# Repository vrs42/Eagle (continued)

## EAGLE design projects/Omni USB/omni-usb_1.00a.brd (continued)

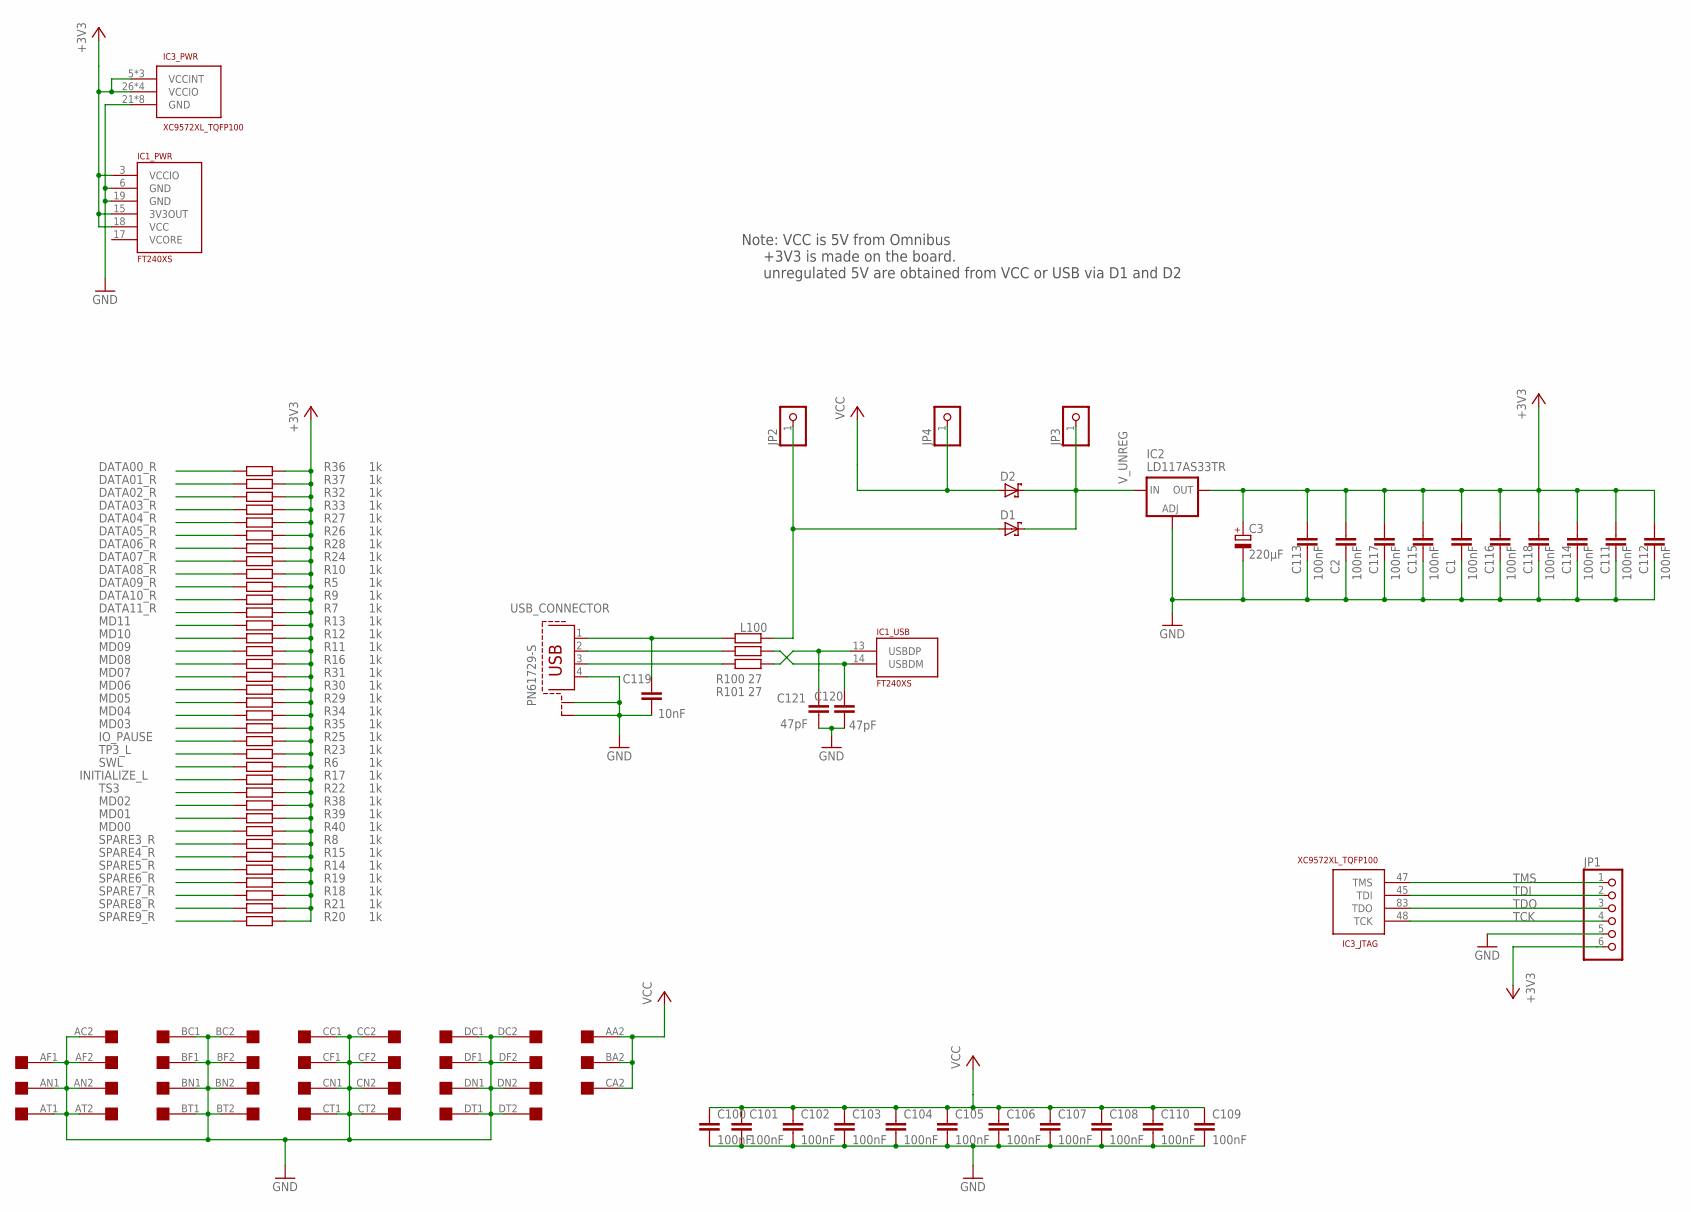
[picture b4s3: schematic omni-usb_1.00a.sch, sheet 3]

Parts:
C1, C2, C100, C101, C102, C103, C104, C105, C106, C107, C108, C109, C110, C111, C112, C113, C114, C115, C116, C117, C118: 100nF; C0805; MPN 08053C104KAT2A
C3: 220µF; SANYO-OSCON_SMD_F8; MPN MCEEL10V227M8X10.5
C119: 10nF; C0805; MPN 08055C103KAT2A
C120, C121: 47pF; C0805; MPN MCCA000326
D1, D2: SCHOTTKY-DIODESMD; SMB; MPN BAT165
IC1: FT240XS; TSSOP24; MPN FT240XS
IC2: LD117AS33TR; SOT223; MPN TLV1117-33CDCY
IC3: XC9572XL_TQFP100; TQ100; MPN XC9572XL-10TQG100C
JP1: PINHD-1X6/90; 1X06/90; MPN MC34751
JP2, JP3, JP4: PINHD-1X1; 1X01
L100: R-EU_R0805; R0805
R5, R6, R7, R8, R9, R10, R11, R12, R13, R14, R15, R16, R17, R18, R19, R20, R21, R22, R23, R24, R25, R26, R27, R28, R29, R30, R31, R32, R33, R34, R35, R36, R37, R38, R39, R40: 1k; R0805; MPN ERJ6GEYJ102V
R100, R101: 27; R0805; MPN ERJ6ENF2742V
U$2: QUAD; EDGE-CON8
USB_CONNECTOR: PN61729-S; MPN MC32596

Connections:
+3V3: C1.1, C2.1, C3.+, C111.1, C112.1, C113.1, C114.1, C115.1, C116.1, C117.1, C118.1, IC1.3 (VCCIO), IC1.15 (3V3OUT), IC1.18 (VCC), IC2.4 (OUT), IC3.5 (VCCINT), IC3.26 (VCCIO), IC3.38 (VCCIO), IC3.51 (VCCIO), IC3.57 (VCCINT), IC3.88 (VCCIO), IC3.98 (VCCINT), JP1.6, R5.1, R6.1, R7.1, R8.1, R9.1, R10.1, R11.1, R12.1, R13.1, R14.1, R15.1, R16.1, R17.1, R18.1, R19.1, R20.1, R21.1, R22.1, R23.1, R24.1, R25.1, R26.1, R27.1, R28.1, R29.1, R30.1, R31.1, R32.1, R33.1, R34.1, R35.1, R36.1, R37.1, R38.1, R39.1, R40.1; also elsewhere on the board
DATA00_R: R36.2; also elsewhere on the board
DATA01_R: R37.2; also elsewhere on the board
DATA02_R: R32.2; also elsewhere on the board
DATA03_R: R33.2; also elsewhere on the board
DATA04_R: R27.2; also elsewhere on the board
DATA05_R: R26.2; also elsewhere on the board
DATA06_R: R28.2; also elsewhere on the board
DATA07_R: R24.2; also elsewhere on the board
DATA08_R: R10.2; also elsewhere on the board
DATA09_R: R5.2; also elsewhere on the board
DATA10_R: R9.2; also elsewhere on the board
DATA11_R: R7.2; also elsewhere on the board
GND: C1.2, C2.2, C3.-, C100.2, C101.2, C102.2, C103.2, C104.2, C105.2, C106.2, C107.2, C108.2, C109.2, C110.2, C111.2, C112.2, C113.2, C114.2, C115.2, C116.2, C117.2, C118.2, C119.2, C120.2, C121.2, IC1.6 (GND), IC1.19 (GND), IC2.1 (ADJ), IC3.21 (GND), IC3.31 (GND), IC3.44 (GND), IC3.62 (GND), IC3.69 (GND), IC3.75 (GND), IC3.84 (GND), IC3.100 (GND), JP1.5, U$2.AC2, U$2.AF1, U$2.AF2, U$2.AN1, U$2.AN2, U$2.AT1, U$2.AT2, U$2.BC1, U$2.BC2, U$2.BF1, U$2.BF2, U$2.BN1, U$2.BN2, U$2.BT1, U$2.BT2, U$2.CC1, U$2.CC2, U$2.CF1, U$2.CF2, U$2.CN1, U$2.CN2, U$2.CT1, U$2.CT2, U$2.DC1, U$2.DC2, U$2.DF1, U$2.DF2, U$2.DN1, U$2.DN2, U$2.DT1, U$2.DT2, USB_CONNECTOR.4, USB_CONNECTOR.S1, USB_CONNECTOR.S2; also elsewhere on the board
INITIALIZE_L: R17.2; also elsewhere on the board
IO_PAUSE: R25.2; also elsewhere on the board
MD00: R40.2; also elsewhere on the board
MD01: R39.2; also elsewhere on the board
MD02: R38.2; also elsewhere on the board
MD03: R35.2; also elsewhere on the board
MD04: R34.2; also elsewhere on the board
MD05: R29.2; also elsewhere on the board
MD06: R30.2; also elsewhere on the board
MD07: R31.2; also elsewhere on the board
MD08: R16.2; also elsewhere on the board
MD09: R11.2; also elsewhere on the board
MD10: R12.2; also elsewhere on the board
MD11: R13.2; also elsewhere on the board
unnamed: C121.1, IC1.13 (USBDP), R101.2
unnamed: C119.1, L100.2, USB_CONNECTOR.1
unnamed: C120.1, IC1.14 (USBDM), R100.2
unnamed: R100.1, USB_CONNECTOR.2
unnamed: R101.1, USB_CONNECTOR.3
SPARE3_R: R8.2; also elsewhere on the board
SPARE4_R: R15.2; also elsewhere on the board
SPARE5_R: R14.2; also elsewhere on the board
SPARE6_R: R19.2; also elsewhere on the board
SPARE7_R: R18.2; also elsewhere on the board
SPARE8_R: R21.2; also elsewhere on the board
SPARE9_R: R20.2; also elsewhere on the board
SWL: R6.2; also elsewhere on the board
TCK: IC3.48 (TCK), JP1.4
TDI: IC3.45 (TDI), JP1.2
TDO: IC3.83 (TDO), JP1.3
TMS: IC3.47 (TMS), JP1.1
TP3_L: R23.2; also elsewhere on the board
TS3: R22.2; also elsewhere on the board
VCC: C100.1, C101.1, C102.1, C103.1, C104.1, C105.1, C106.1, C107.1, C108.1, C109.1, C110.1, D2.A, JP4.1, U$2.AA2, U$2.BA2, U$2.CA2; also elsewhere on the board
V_UNREG: D1.C, D2.C, IC2.3 (IN), JP3.1
V_USB: D1.A, JP2.1, L100.1

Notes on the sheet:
Note: VCC is 5V from Omnibus +3V3 is made on the board. unregulated 5V are obtained from VCC or USB via D1 and D2

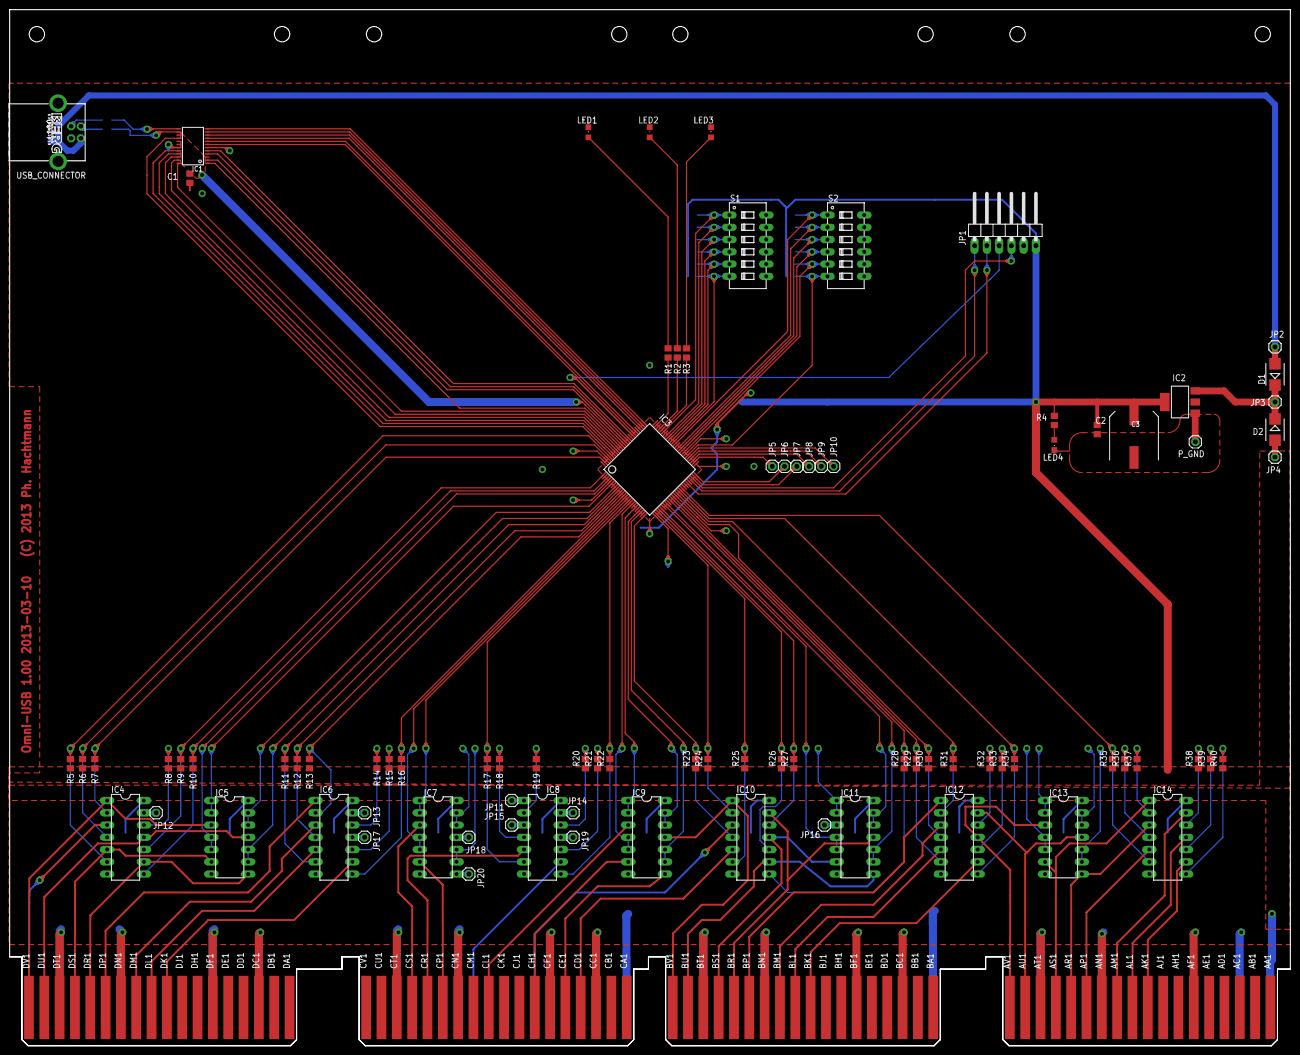
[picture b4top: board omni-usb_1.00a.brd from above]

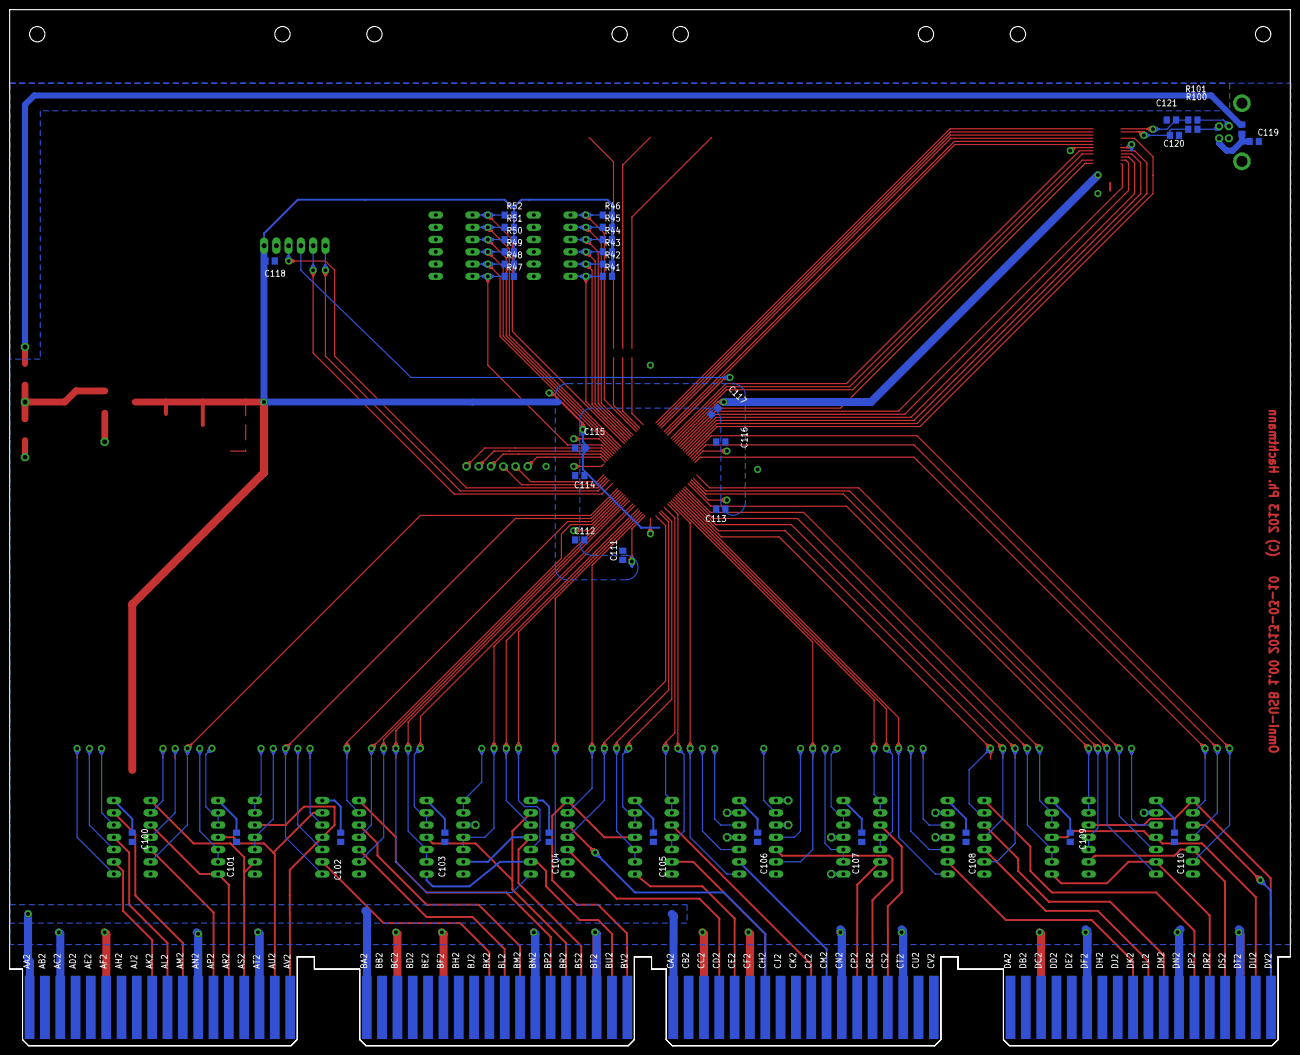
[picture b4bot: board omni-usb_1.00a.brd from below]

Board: 2 copper layers, 265.3 x 214.6 mm, 126 parts (37 on the bottom side), 155 nets.

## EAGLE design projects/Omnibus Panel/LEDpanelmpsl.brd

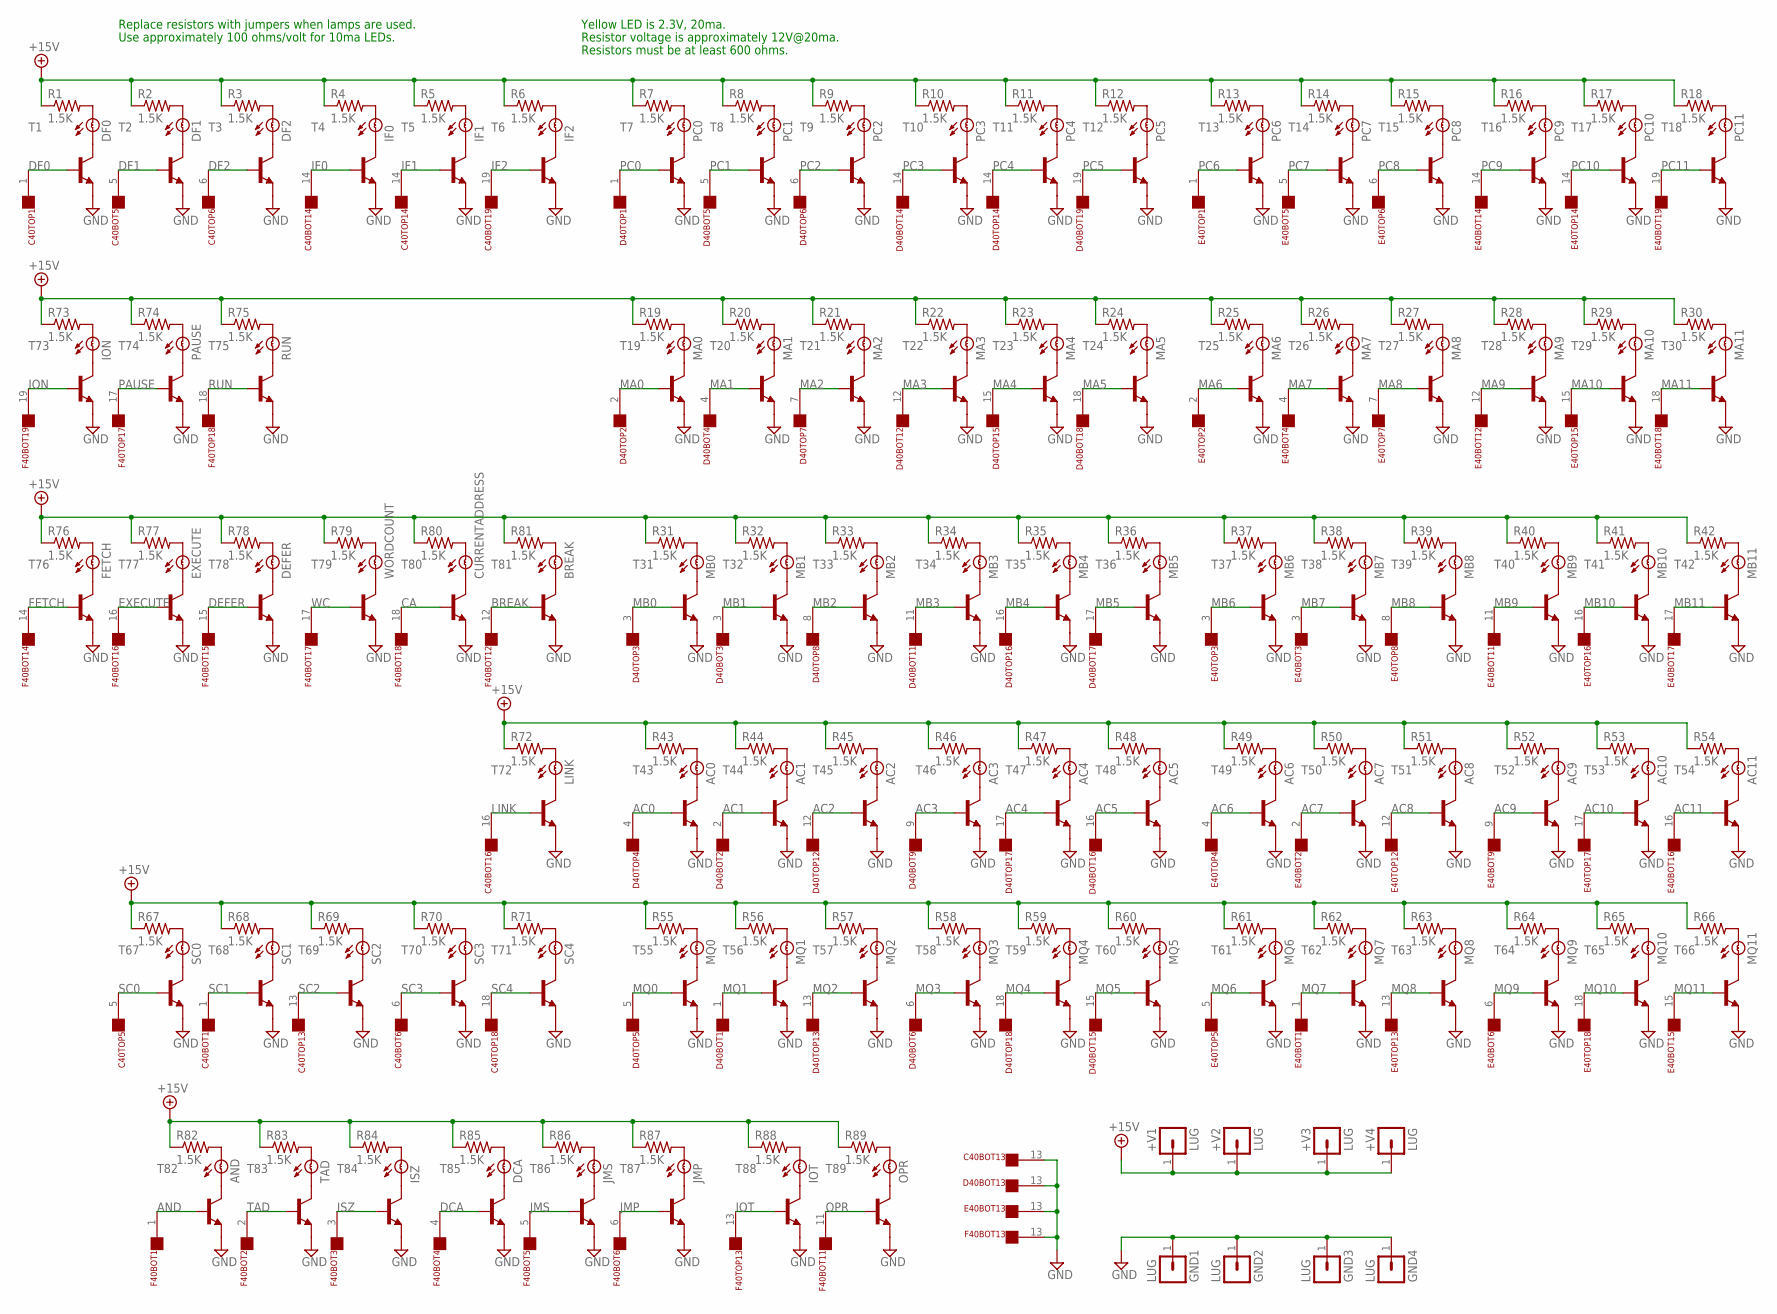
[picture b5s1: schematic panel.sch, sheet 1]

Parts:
+V1, +V2, +V3, +V4: LUG; SPADELUG
AC0, AC1, AC2, AC3, AC4, AC5, AC6, AC7, AC8, AC9, AC10, AC11: BULB
AND: BULB
BREAK: BULB
C40BOT, C40TOP: FLEX19
CURRENTADDRESS: BULB
D40BOT, D40TOP: FLEX19
DCA: BULB
DEFER: BULB
DF0, DF1, DF2: BULB
E40BOT, E40TOP: FLEX19
EXECUTE: BULB
F40BOT, F40TOP: FLEX19
FETCH: BULB
GND1, GND2, GND3, GND4: LUG; SPADELUG
IF0, IF1, IF2: BULB
ION: BULB
IOT: BULB
ISZ: BULB
JMP: BULB
JMS: BULB
LINK: BULB
MA0, MA1, MA2, MA3, MA4, MA5, MA6, MA7, MA8, MA9, MA10, MA11: BULB
MB0, MB1, MB2, MB3, MB4, MB5, MB6, MB7, MB8, MB9, MB10, MB11: BULB
MQ0, MQ1, MQ2, MQ3, MQ4, MQ5, MQ6, MQ7, MQ8, MQ9, MQ10, MQ11: BULB
OPR: BULB
PAUSE: BULB
PC0, PC1, PC2, PC3, PC4, PC5, PC6, PC7, PC8, PC9, PC10, PC11: BULB
R1, R2, R3, R4, R5, R6, R7, R8, R9, R10, R11, R12, R13, R14, R15, R16, R17, R18, R19, R20, R21, R22, R23, R24, R25, R26, R27, R28, R29, R30, R31, R32, R33, R34, R35, R36, R37, R38, R39, R40, R41, R42, R43, R44, R45, R46, R47, R48, R49, R50, R51, R52, R53, R54, R55, R56, R57, R58, R59, R60, R61, R62, R63, R64, R65, R66, R67, R68, R69, R70, R71, R72, R73, R74, R75, R76, R77, R78, R79, R80, R81, R82, R83, R84, R85, R86, R87, R88, R89: 1.5K; 0207/10
RUN: BULB
SC0, SC1, SC2, SC3, SC4: BULB
T1, T2, T3, T4, T5, T6, T7, T8, T9, T10, T11, T12, T13, T14, T15, T16, T17, T18, T19, T20, T21, T22, T23, T24, T25, T26, T27, T28, T29, T30, T31, T32, T33, T34, T35, T36, T37, T38, T39, T40, T41, T42, T43, T44, T45, T46, T47, T48, T49, T50, T51, T52, T53, T54, T55, T56, T57, T58, T59, T60, T61, T62, T63, T64, T65, T66, T67, T68, T69, T70, T71, T72, T73, T74, T75, T76, T77, T78, T79, T80, T81, T82, T83, T84, T85, T86, T87, T88, T89: MPS2222A-NPN-TO92-CBE; TO92-CBE
TAD: BULB
WORDCOUNT: BULB

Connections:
+15V: +V1.1, +V2.1, +V3.1, +V4.1, R1.1, R2.1, R3.1, R4.1, R5.1, R6.1, R7.1, R8.1, R9.1, R10.1, R11.1, R12.1, R13.1, R14.1, R15.1, R16.1, R17.1, R18.1, R19.1, R20.1, R21.1, R22.1, R23.1, R24.1, R25.1, R26.1, R27.1, R28.1, R29.1, R30.1, R31.1, R32.1, R33.1, R34.1, R35.1, R36.1, R37.1, R38.1, R39.1, R40.1, R41.1, R42.1, R43.1, R44.1, R45.1, R46.1, R47.1, R48.1, R49.1, R50.1, R51.1, R52.1, R53.1, R54.1, R55.1, R56.1, R57.1, R58.1, R59.1, R60.1, R61.1, R62.1, R63.1, R64.1, R65.1, R66.1, R67.1, R68.1, R69.1, R70.1, R71.1, R72.1, R73.1, R74.1, R75.1, R76.1, R77.1, R78.1, R79.1, R80.1, R81.1, R82.1, R83.1, R84.1, R85.1, R86.1, R87.1, R88.1, R89.1
AC0: D40TOP.4, T43.B; also elsewhere on the board
AC1: D40BOT.2, T44.B; also elsewhere on the board
AC2: D40TOP.12, T45.B; also elsewhere on the board
AC3: D40BOT.9, T46.B; also elsewhere on the board
AC4: D40TOP.17, T47.B; also elsewhere on the board
AC5: D40BOT.16, T48.B; also elsewhere on the board
AC6: E40TOP.4, T49.B; also elsewhere on the board
AC7: E40BOT.2, T50.B; also elsewhere on the board
AC8: E40TOP.12, T51.B; also elsewhere on the board
AC9: E40BOT.9, T52.B; also elsewhere on the board
AC10: E40TOP.17, T53.B; also elsewhere on the board
AC11: E40BOT.16, T54.B; also elsewhere on the board
AND: F40BOT.1, T82.B; also elsewhere on the board
BREAK: F40BOT.12, T81.B; also elsewhere on the board
CA: F40BOT.18, T80.B; also elsewhere on the board
DCA: F40BOT.4, T85.B; also elsewhere on the board
DEFER: F40BOT.15, T78.B; also elsewhere on the board
DF0: C40TOP.1, T1.B; also elsewhere on the board
DF1: C40BOT.5, T2.B; also elsewhere on the board
DF2: C40TOP.6, T3.B; also elsewhere on the board
EXECUTE: F40BOT.16, T77.B; also elsewhere on the board
FETCH: F40BOT.14, T76.B; also elsewhere on the board
GND: C40BOT.13, D40BOT.13, E40BOT.13, F40BOT.13, GND1.1, GND2.1, GND3.1, GND4.1, T1.E, T2.E, T3.E, T4.E, T5.E, T6.E, T7.E, T8.E, T9.E, T10.E, T11.E, T12.E, T13.E, T14.E, T15.E, T16.E, T17.E, T18.E, T19.E, T20.E, T21.E, T22.E, T23.E, T24.E, T25.E, T26.E, T27.E, T28.E, T29.E, T30.E, T31.E, T32.E, T33.E, T34.E, T35.E, T36.E, T37.E, T38.E, T39.E, T40.E, T41.E, T42.E, T43.E, T44.E, T45.E, T46.E, T47.E, T48.E, T49.E, T50.E, T51.E, T52.E, T53.E, T54.E, T55.E, T56.E, T57.E, T58.E, T59.E, T60.E, T61.E, T62.E, T63.E, T64.E, T65.E, T66.E, T67.E, T68.E, T69.E, T70.E, T71.E, T72.E, T73.E, T74.E, T75.E, T76.E, T77.E, T78.E, T79.E, T80.E, T81.E, T82.E, T83.E, T84.E, T85.E, T86.E, T87.E, T88.E, T89.E; also elsewhere on the board
IF0: C40BOT.14, T4.B; also elsewhere on the board
IF1: C40TOP.14, T5.B; also elsewhere on the board
IF2: C40BOT.19, T6.B; also elsewhere on the board
ION: F40BOT.19, T73.B; also elsewhere on the board
IOT: F40TOP.13, T88.B; also elsewhere on the board
ISZ: F40BOT.3, T84.B; also elsewhere on the board
JMP: F40BOT.6, T87.B; also elsewhere on the board
JMS: F40BOT.5, T86.B; also elsewhere on the board
LINK: C40BOT.16, T72.B; also elsewhere on the board
MA0: D40TOP.2, T19.B; also elsewhere on the board
MA1: D40BOT.4, T20.B; also elsewhere on the board
MA2: D40TOP.7, T21.B; also elsewhere on the board
MA3: D40BOT.12, T22.B; also elsewhere on the board
MA4: D40TOP.15, T23.B; also elsewhere on the board
MA5: D40BOT.18, T24.B; also elsewhere on the board
MA6: E40TOP.2, T25.B; also elsewhere on the board
MA7: E40BOT.4, T26.B; also elsewhere on the board
MA8: E40TOP.7, T27.B; also elsewhere on the board
MA9: E40BOT.12, T28.B; also elsewhere on the board
MA10: E40TOP.15, T29.B; also elsewhere on the board
MA11: E40BOT.18, T30.B; also elsewhere on the board
MB0: D40TOP.3, T31.B; also elsewhere on the board
MB1: D40BOT.3, T32.B; also elsewhere on the board
MB2: D40TOP.8, T33.B; also elsewhere on the board
MB3: D40BOT.11, T34.B; also elsewhere on the board
MB4: D40TOP.16, T35.B; also elsewhere on the board
MB5: D40BOT.17, T36.B; also elsewhere on the board
MB6: E40TOP.3, T37.B; also elsewhere on the board
MB7: E40BOT.3, T38.B; also elsewhere on the board
MB8: E40TOP.8, T39.B; also elsewhere on the board
MB9: E40BOT.11, T40.B; also elsewhere on the board
MB10: E40TOP.16, T41.B; also elsewhere on the board
MB11: E40BOT.17, T42.B; also elsewhere on the board
MQ0: D40TOP.5, T55.B; also elsewhere on the board
MQ1: D40BOT.1, T56.B; also elsewhere on the board
MQ2: D40TOP.13, T57.B; also elsewhere on the board
MQ3: D40BOT.6, T58.B; also elsewhere on the board
MQ4: D40TOP.18, T59.B; also elsewhere on the board
MQ5: D40BOT.15, T60.B; also elsewhere on the board
MQ6: E40TOP.5, T61.B; also elsewhere on the board
MQ7: E40BOT.1, T62.B; also elsewhere on the board
MQ8: E40TOP.13, T63.B; also elsewhere on the board
MQ9: E40BOT.6, T64.B; also elsewhere on the board
MQ10: E40TOP.18, T65.B; also elsewhere on the board
MQ11: E40BOT.15, T66.B; also elsewhere on the board
unnamed: DF0.B, T1.C
unnamed: DF1.B, T2.C
unnamed: DF2.B, T3.C
unnamed: IF0.B, T4.C
unnamed: IF1.B, T5.C
unnamed: IF2.B, T6.C
unnamed: PC0.B, T7.C
unnamed: PC1.B, T8.C
unnamed: PC2.B, T9.C
unnamed: PC3.B, T10.C
unnamed: PC4.B, T11.C
unnamed: PC5.B, T12.C
unnamed: PC6.B, T13.C
unnamed: PC7.B, T14.C
unnamed: PC8.B, T15.C
unnamed: PC9.B, T16.C
unnamed: PC10.B, T17.C
unnamed: PC11.B, T18.C
unnamed: MA0.B, T19.C
unnamed: MA1.B, T20.C
unnamed: MA2.B, T21.C
unnamed: MA3.B, T22.C
unnamed: MA4.B, T23.C
unnamed: MA5.B, T24.C
unnamed: MA6.B, T25.C
unnamed: MA7.B, T26.C
unnamed: MA8.B, T27.C
unnamed: MA9.B, T28.C
unnamed: MA10.B, T29.C
unnamed: MA11.B, T30.C
unnamed: MB0.B, T31.C
unnamed: MB1.B, T32.C
unnamed: MB2.B, T33.C
unnamed: MB3.B, T34.C
unnamed: MB4.B, T35.C
unnamed: MB5.B, T36.C
unnamed: MB6.B, T37.C
unnamed: MB7.B, T38.C
unnamed: MB8.B, T39.C
unnamed: MB9.B, T40.C
unnamed: MB10.B, T41.C
unnamed: MB11.B, T42.C
unnamed: AC0.B, T43.C
unnamed: AC1.B, T44.C
unnamed: AC2.B, T45.C
unnamed: AC3.B, T46.C
unnamed: AC4.B, T47.C
unnamed: AC5.B, T48.C
unnamed: AC6.B, T49.C
unnamed: AC7.B, T50.C
unnamed: AC8.B, T51.C
unnamed: AC9.B, T52.C
unnamed: AC10.B, T53.C
unnamed: AC11.B, T54.C
unnamed: MQ0.B, T55.C
unnamed: MQ1.B, T56.C
unnamed: MQ2.B, T57.C
unnamed: MQ3.B, T58.C
unnamed: MQ4.B, T59.C
unnamed: MQ5.B, T60.C
unnamed: MQ6.B, T61.C
unnamed: MQ7.B, T62.C
unnamed: MQ8.B, T63.C
unnamed: MQ9.B, T64.C
unnamed: MQ10.B, T65.C
unnamed: MQ11.B, T66.C
unnamed: SC0.B, T67.C
unnamed: SC1.B, T68.C
unnamed: SC2.B, T69.C
unnamed: SC3.B, T70.C
unnamed: SC4.B, T71.C
unnamed: LINK.B, T72.C
unnamed: ION.B, T73.C
unnamed: PAUSE.B, T74.C
unnamed: RUN.B, T75.C
unnamed: FETCH.B, T76.C
unnamed: EXECUTE.B, T77.C
unnamed: DEFER.B, T78.C
unnamed: T79.C, WORDCOUNT.B
unnamed: CURRENTADDRESS.B, T80.C
unnamed: BREAK.B, T81.C
unnamed: AND.B, T82.C
unnamed: T83.C, TAD.B
unnamed: ISZ.B, T84.C
unnamed: DCA.B, T85.C
unnamed: JMS.B, T86.C
unnamed: JMP.B, T87.C
unnamed: IOT.B, T88.C
unnamed: OPR.B, T89.C
unnamed: DF0.A, R1.2
unnamed: DF1.A, R2.2
unnamed: DF2.A, R3.2
unnamed: IF0.A, R4.2
unnamed: IF1.A, R5.2
unnamed: IF2.A, R6.2
unnamed: PC0.A, R7.2
unnamed: PC1.A, R8.2
unnamed: PC2.A, R9.2
unnamed: PC3.A, R10.2
unnamed: PC4.A, R11.2
unnamed: PC5.A, R12.2
unnamed: PC6.A, R13.2
unnamed: PC7.A, R14.2
unnamed: PC8.A, R15.2
unnamed: PC9.A, R16.2
unnamed: PC10.A, R17.2
unnamed: PC11.A, R18.2
unnamed: ION.A, R73.2
unnamed: PAUSE.A, R74.2
unnamed: R75.2, RUN.A
unnamed: MA0.A, R19.2
unnamed: MA1.A, R20.2
unnamed: MA2.A, R21.2
unnamed: MA3.A, R22.2
unnamed: MA4.A, R23.2
unnamed: MA5.A, R24.2
unnamed: MA6.A, R25.2
unnamed: MA7.A, R26.2
unnamed: MA8.A, R27.2
unnamed: MA9.A, R28.2
unnamed: MA10.A, R29.2
unnamed: MA11.A, R30.2
unnamed: FETCH.A, R76.2
unnamed: EXECUTE.A, R77.2
unnamed: DEFER.A, R78.2
unnamed: R79.2, WORDCOUNT.A
unnamed: CURRENTADDRESS.A, R80.2
unnamed: BREAK.A, R81.2
unnamed: LINK.A, R72.2
unnamed: MB0.A, R31.2
unnamed: MB1.A, R32.2
unnamed: MB2.A, R33.2
unnamed: MB3.A, R34.2
unnamed: MB4.A, R35.2
unnamed: MB5.A, R36.2
unnamed: MB6.A, R37.2
unnamed: MB7.A, R38.2
unnamed: MB8.A, R39.2
unnamed: MB9.A, R40.2
unnamed: MB10.A, R41.2
unnamed: MB11.A, R42.2
unnamed: AC0.A, R43.2
unnamed: AC1.A, R44.2
unnamed: AC2.A, R45.2
unnamed: AC3.A, R46.2
unnamed: AC4.A, R47.2
unnamed: AC5.A, R48.2
unnamed: AC6.A, R49.2
unnamed: AC7.A, R50.2
unnamed: AC8.A, R51.2
unnamed: AC9.A, R52.2
unnamed: AC10.A, R53.2
unnamed: AC11.A, R54.2
unnamed: R67.2, SC0.A
unnamed: R68.2, SC1.A
unnamed: R69.2, SC2.A
unnamed: R70.2, SC3.A
unnamed: R71.2, SC4.A
unnamed: MQ11.A, R66.2
unnamed: MQ10.A, R65.2
unnamed: MQ9.A, R64.2
unnamed: MQ8.A, R63.2
unnamed: MQ7.A, R62.2
unnamed: MQ6.A, R61.2
unnamed: MQ5.A, R60.2
unnamed: MQ4.A, R59.2
unnamed: MQ3.A, R58.2
unnamed: MQ2.A, R57.2
unnamed: MQ1.A, R56.2
unnamed: MQ0.A, R55.2
unnamed: AND.A, R82.2
unnamed: R83.2, TAD.A
unnamed: ISZ.A, R84.2
unnamed: DCA.A, R85.2
unnamed: JMS.A, R86.2
unnamed: JMP.A, R87.2
unnamed: IOT.A, R88.2
unnamed: OPR.A, R89.2
OPR: F40BOT.11, T89.B; also elsewhere on the board
PAUSE: F40TOP.17, T74.B; also elsewhere on the board
PC0: D40TOP.1, T7.B; also elsewhere on the board
PC1: D40BOT.5, T8.B; also elsewhere on the board
PC2: D40TOP.6, T9.B; also elsewhere on the board
PC3: D40BOT.14, T10.B; also elsewhere on the board
PC4: D40TOP.14, T11.B; also elsewhere on the board
PC5: D40BOT.19, T12.B; also elsewhere on the board
PC6: E40TOP.1, T13.B; also elsewhere on the board
PC7: E40BOT.5, T14.B; also elsewhere on the board
PC8: E40TOP.6, T15.B; also elsewhere on the board
PC9: E40BOT.14, T16.B; also elsewhere on the board
PC10: E40TOP.14, T17.B; also elsewhere on the board
PC11: E40BOT.19, T18.B; also elsewhere on the board
RUN: F40TOP.18, T75.B; also elsewhere on the board
SC0: C40TOP.5, T67.B; also elsewhere on the board
SC1: C40BOT.1, T68.B; also elsewhere on the board
SC2: C40TOP.13, T69.B; also elsewhere on the board
SC3: C40BOT.6, T70.B; also elsewhere on the board
SC4: C40TOP.18, T71.B; also elsewhere on the board
TAD: F40BOT.2, T83.B; also elsewhere on the board
WC: F40BOT.17, T79.B; also elsewhere on the board

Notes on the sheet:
Replace resistors with jumpers when lamps are used.
Use approximately 100 ohms/volt for 10ma LEDs.
Yellow LED is 2.3V, 20ma.
Resistor voltage is approximately 12V@20ma.
Resistors must be at least 600 ohms.

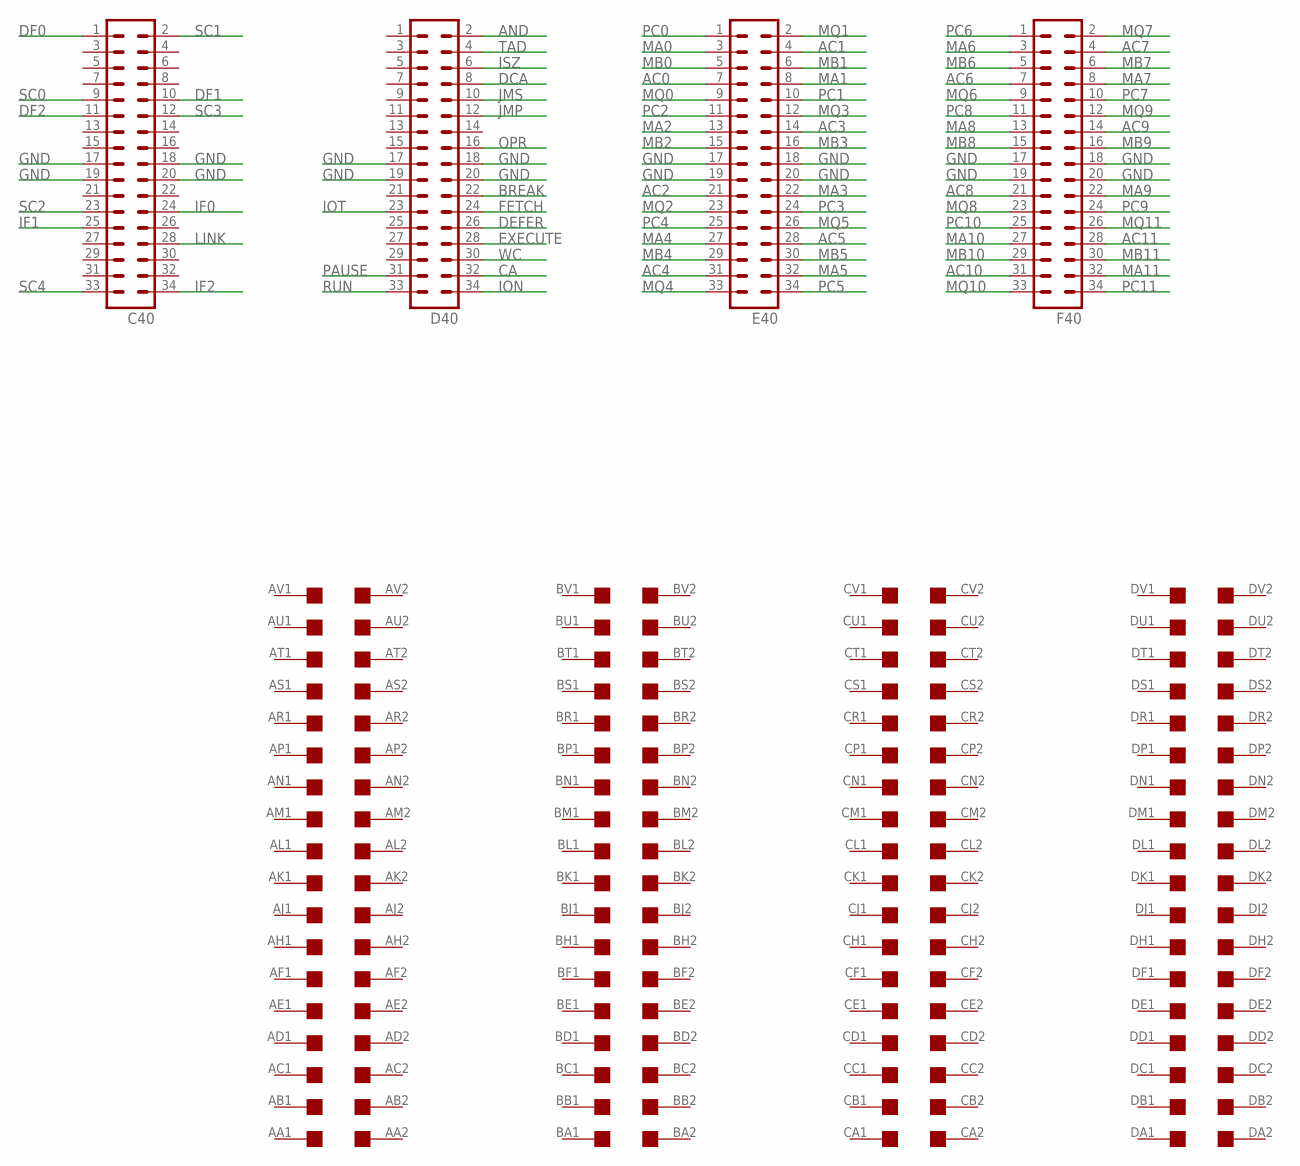
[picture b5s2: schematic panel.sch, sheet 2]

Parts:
C40: MA17-2
D40: MA17-2
E40: MA17-2
F40: MA17-2
U$10: QUAD; EDGE-CON8

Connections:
AC0: E40.7; also elsewhere on the board
AC1: E40.4; also elsewhere on the board
AC2: E40.21; also elsewhere on the board
AC3: E40.14; also elsewhere on the board
AC4: E40.31; also elsewhere on the board
AC5: E40.28; also elsewhere on the board
AC6: F40.7; also elsewhere on the board
AC7: F40.4; also elsewhere on the board
AC8: F40.21; also elsewhere on the board
AC9: F40.14; also elsewhere on the board
AC10: F40.31; also elsewhere on the board
AC11: F40.28; also elsewhere on the board
AND: D40.2; also elsewhere on the board
BREAK: D40.22; also elsewhere on the board
CA: D40.32; also elsewhere on the board
DCA: D40.8; also elsewhere on the board
DEFER: D40.26; also elsewhere on the board
DF0: C40.1; also elsewhere on the board
DF1: C40.10; also elsewhere on the board
DF2: C40.11; also elsewhere on the board
EXECUTE: D40.28; also elsewhere on the board
FETCH: D40.24; also elsewhere on the board
GND: C40.17, C40.18, C40.19, C40.20, D40.17, D40.18, D40.19, D40.20, E40.17, E40.18, E40.19, E40.20, F40.17, F40.18, F40.19, F40.20; also elsewhere on the board
IF0: C40.24; also elsewhere on the board
IF1: C40.25; also elsewhere on the board
IF2: C40.34; also elsewhere on the board
ION: D40.34; also elsewhere on the board
IOT: D40.23; also elsewhere on the board
ISZ: D40.6; also elsewhere on the board
JMP: D40.12; also elsewhere on the board
JMS: D40.10; also elsewhere on the board
LINK: C40.28; also elsewhere on the board
MA0: E40.3; also elsewhere on the board
MA1: E40.8; also elsewhere on the board
MA2: E40.13; also elsewhere on the board
MA3: E40.22; also elsewhere on the board
MA4: E40.27; also elsewhere on the board
MA5: E40.32; also elsewhere on the board
MA6: F40.3; also elsewhere on the board
MA7: F40.8; also elsewhere on the board
MA8: F40.13; also elsewhere on the board
MA9: F40.22; also elsewhere on the board
MA10: F40.27; also elsewhere on the board
MA11: F40.32; also elsewhere on the board
MB0: E40.5; also elsewhere on the board
MB1: E40.6; also elsewhere on the board
MB2: E40.15; also elsewhere on the board
MB3: E40.16; also elsewhere on the board
MB4: E40.29; also elsewhere on the board
MB5: E40.30; also elsewhere on the board
MB6: F40.5; also elsewhere on the board
MB7: F40.6; also elsewhere on the board
MB8: F40.15; also elsewhere on the board
MB9: F40.16; also elsewhere on the board
MB10: F40.29; also elsewhere on the board
MB11: F40.30; also elsewhere on the board
MQ0: E40.9; also elsewhere on the board
MQ1: E40.2; also elsewhere on the board
MQ2: E40.23; also elsewhere on the board
MQ3: E40.12; also elsewhere on the board
MQ4: E40.33; also elsewhere on the board
MQ5: E40.26; also elsewhere on the board
MQ6: F40.9; also elsewhere on the board
MQ7: F40.2; also elsewhere on the board
MQ8: F40.23; also elsewhere on the board
MQ9: F40.12; also elsewhere on the board
MQ10: F40.33; also elsewhere on the board
MQ11: F40.26; also elsewhere on the board
OPR: D40.16; also elsewhere on the board
PAUSE: D40.31; also elsewhere on the board
PC0: E40.1; also elsewhere on the board
PC1: E40.10; also elsewhere on the board
PC2: E40.11; also elsewhere on the board
PC3: E40.24; also elsewhere on the board
PC4: E40.25; also elsewhere on the board
PC5: E40.34; also elsewhere on the board
PC6: F40.1; also elsewhere on the board
PC7: F40.10; also elsewhere on the board
PC8: F40.11; also elsewhere on the board
PC9: F40.24; also elsewhere on the board
PC10: F40.25; also elsewhere on the board
PC11: F40.34; also elsewhere on the board
RUN: D40.33; also elsewhere on the board
SC0: C40.9; also elsewhere on the board
SC1: C40.2; also elsewhere on the board
SC2: C40.23; also elsewhere on the board
SC3: C40.12; also elsewhere on the board
SC4: C40.33; also elsewhere on the board
TAD: D40.4; also elsewhere on the board
WC: D40.30; also elsewhere on the board

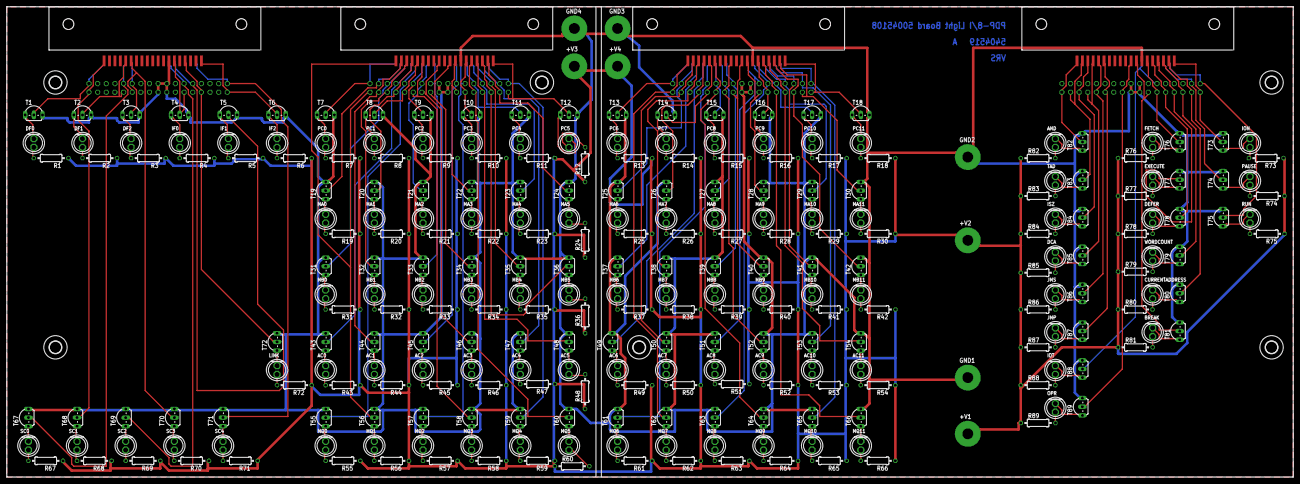
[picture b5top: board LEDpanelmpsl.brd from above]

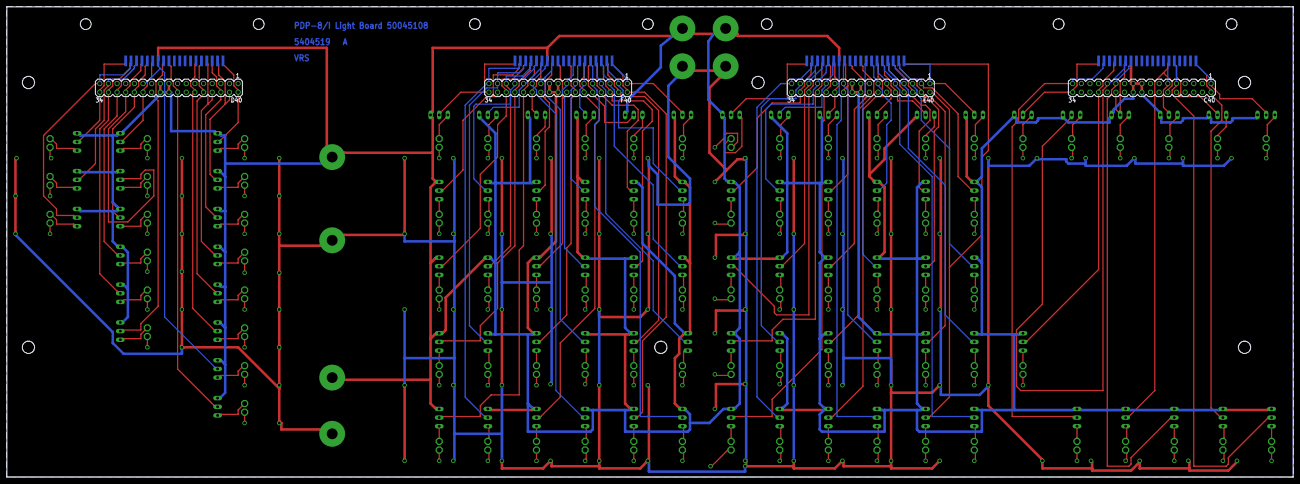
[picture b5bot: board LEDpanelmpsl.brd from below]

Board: 2 copper layers, 377.8 x 138.1 mm, 297 parts (8 on the bottom side), 269 nets.

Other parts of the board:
U$1, U$2, U$3, U$4: STRAIN-RELIEF
U$5, U$6, U$7, U$8, U$9, U$11: 3,6

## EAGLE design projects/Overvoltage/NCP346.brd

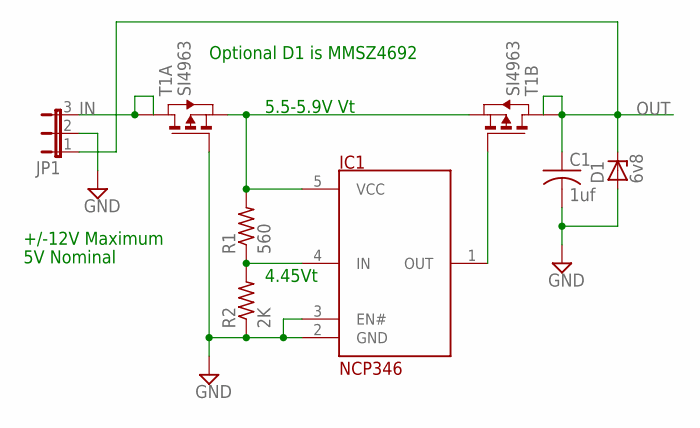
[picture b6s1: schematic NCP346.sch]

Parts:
C1: 1uf; C1206
D1: 6v8; SOD80C
IC1: NCP346; SOT23-5
JP1: JP2W
R1: 560; R0603
R2: 2K; R0603
T1: SI4963; SO8

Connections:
GND: C1.2, D1.A, IC1.2 (GND), IC1.3 (EN#), JP1.2, R2.1, T1.4 (G)
IN: JP1.3, T1.5 (D), T1.6 (D1)
unnamed: IC1.1 (OUT), T1.2 (G)
unnamed: IC1.4 (IN), R1.1, R2.2
OUT: C1.1, D1.C, JP1.1, T1.7 (D), T1.8 (D1)
VCC: IC1.5 (VCC), R1.2, T1.1 (S), T1.3 (S)

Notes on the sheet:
4.45Vt
+/-12V Maximum
5V Nominal
5.5-5.9V Vt
Optional D1 is MMSZ4692
